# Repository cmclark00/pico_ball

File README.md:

# pico_ball — carry your Pokémon out of a real cartridge

Turn a [`weimanc/game-boy-zero-link-board`](https://github.com/weimanc/game-boy-zero-link-board)
(an RP2040‑Zero USB↔Game Boy Link‑Cable adapter) into a tool that talks to your
**physical Pokémon Blue** cartridge over the link port and **copies a Pokémon off
it into a file you can carry around** — without losing it from the cartridge.

> **Status:** Path A (PC‑tethered extract + inject) is **working on real
> hardware** — both directions, non‑destructive. Path B (fully standalone, no‑PC
> pocket vault) is **built and compiling** (`firmware/prebuilt/pico_ball_vault.uf2`);
> its on‑device trade FSM awaits a hardware bring‑up pass — see
> [firmware/path-b-standalone/README.md](firmware/path-b-standalone/README.md).

## The one important mental‑model correction

Your board is **not** where the Pokémon "lives." It is a *bridge*: it speaks the
Game Boy link‑cable serial protocol on one side and USB on the other. The board
pretends to be a second Game Boy so your cartridge will trade with it. Where the
Pokémon actually gets **stored** is a software choice:

- **Path A — tethered:** the storage is a file on your laptop (`vault/`). You carry
  the laptop/phone. Proven, low‑risk, working today.
- **Path B — standalone:** the storage is the RP2040's own on‑board flash. Press a
  button, it does the trade by itself, the Pokémon lives on the board. You carry
  the board. This is the real dream — and it has been proven possible on similar
  hardware (the Flipper Zero Pokémon‑trading app does exactly this).

## How a Game Boy trade actually works (the part that makes this possible)

- Pokémon Blue is a Game Boy (Gen 1) game. A **GBA plays it in GB‑compatibility
  mode** and the link port behaves as the classic GB serial link, so your board's
  GBC/GBA edge connector works for it.
- A trade is a well‑documented **state machine** (Adan Scotney's spec): handshake →
  random‑seed exchange → two patch lists → a 415‑byte "trade block" containing your
  whole party → pick a Pokémon (`0x60 + index`) → swap.
- **Key trick for *copying without losing*:** the cartridge sends its *entire party*
  (the trade block) *before* either side confirms the swap. We read that block,
  save every Pokémon in it, and then **cancel** the trade. The cartridge keeps
  everything; we keep a copy. Non‑destructive.

## Quick start (Path A)

```bash
# 1. One-time setup: Python deps + the proven trade engine we build on
./scripts/setup.sh

# 2. Flash the board (see firmware/README.md) — stacksmashing gb-link-firmware

# 3. Plug board -> laptop (USB) and board -> GBA link port. Boot Pokémon Blue,
#    go to a Pokémon Center -> Cable Club -> Trade Center, sit at the table.

# 4. Copy your party into the vault (non-destructive). The ./pb launcher runs
#    the host tools in the project venv, so there's nothing to activate:
./pb extract              # saves vault/*.pk1 + vault/*.json, then cancels
./pb extract --gen 2      #   ...or Gold/Silver/Crystal (Gen 2 -> *.pk2)

# Gen 3 (Ruby/Sapphire/Emerald/FireRed/LeafGreen): flash the reconfigurable
# firmware (third_party/gen3/gbusb_reconfigurable.uf2), then multiboot the
# GBA-side trade program and capture:
./pb gen3-boot            # upload Gen3-to-GenX into the GBA's RAM
./pb extract --gen 3      # saves vault/*.pk3 (PKHeX party format)

# 5. See what you've captured (no device needed):
./pb list                 # decoded table: gen, species, level, OT, nickname

# 6. (Optional) Trade a vaulted Pokémon back INTO a cartridge:
./pb inject               # pick from a decoded list; the cart's given-up mon is
                          # auto-saved to the vault, so nothing is lost

# 7. (Optional) Export your captures as a .sav (opens in PKHeX/emulators):
./pb export-sav           # Gen 1 -> vault/pico_ball.sav  (--gen 2 for G/S/C)
```

> Prefer the raw scripts? Every `./pb <cmd>` maps to `python host/<cmd>.py`
> after `source host/.venv/bin/activate` — the launcher just saves the typing.

See **[docs/PLAN.md](docs/PLAN.md)** for the full phased plan, and
**[docs/research.md](docs/research.md)** for everything the design is based on
(with sources).

## Gen 1/2 → Gen 3 "transfer" (Pal-Park-style recreation)

The Game Boy and GBA games have **no native link** — Nintendo's first official
forward-migration was Gen 3 → Gen 4 (Pal Park). So a literal transfer is
impossible, but we can *recreate* a captured Gen 1/2 Pokémon as a legal Gen 3
`.pk3`, exactly like **[Poké Transporter GB](https://github.com/GearsProgress/Poke_Transporter_GB)**
does, using its **[Pokémon Community Conversion Standard](https://github.com/GearsProgress/Pokemon-Community-Conversion-Standard)**
(PCCS, MIT). Species, level, moves, nickname, and OT are kept; PID / IVs / nature
/ ability are generated to match.

There are two ways to do it:

**A. Onto a real Gen 3 cartridge — no flashcart, no PC** (standalone board). The
board **multiboots Poke Transporter GB** into a GBA over the link cable, then
offers a stored Gen 1/2 mon to it; PTGB converts it and writes it to the Gen 3
cartridge's save. You only need the board, a GBA, a Gen 3 cart, and the cable —
hand someone a flashed board and they're set. See
[firmware/path-b-standalone/README.md](firmware/path-b-standalone/README.md)
("Transfer Gen 1/2 → Gen 3"). From the cartridge, the mon rides the official Pal
Park → … → HOME chain on real hardware. **This path is not working yet:** the
board can multiboot PTGB, but PTGB expects to talk to a real Game Boy game (it
clocks the link itself and reads the game's PC boxes through its own protocol),
not to a trade partner — see the status note in that README. What the board can
do instead is convert a stored Gen 1/2 Pokémon itself (it runs PCCS) and trade it
into the Gen 3 cartridge through Gen3-to-GenX; that is built and host-tested but
not yet tried on hardware ("Send a Gen 1/2 Pokémon to a Gen 3 cartridge" in that
README).

**B. As a file, for PKHeX/emulators.** `scripts/setup.sh` also builds a host
converter (PCCS), so pulling captures off the board auto-writes a Gen 3 box `.pk3`
for each Gen 1/2 mon:

```bash
./pb import                         # vault/dex/*.pk1 + vault/dex/gen3/*.pk3
```

The `.pk3` files are 80-byte box records — drag them straight into **PKHeX** (or a
Gen 3 save). Run `python tools/test_pccs.py` to self-check the conversion.

Both use the same engine (PCCS), so they produce the same conversion. The endgame
is **Pokémon HOME**: a Gen 1/2 mon → Gen 3 → (Pal Park) Gen 4 → 5 → 6/7 → Bank →
HOME, legal at each hop. The board does the one step with no official path (Gen
1/2 → Gen 3); the rest is the standard forward-migration chain.

## View Pokémon straight from the device (WebUI)

With the standalone (Path B) firmware flashed, you don't need to copy anything to
disk to look at your captures:

```bash
./pb webui                # serves webui/ — open http://localhost:8000 in Chrome/Edge
```

Click **Connect device**, pick **"pico_ball vault"** from the WebUSB chooser, and
the page reads the stored records over **WebUSB** and decodes the Pokémon **in the
browser** — sprite, level, HP, moves, OT. Works on desktop and Android Chrome. See
[webui/README.md](webui/README.md).

## Optional 3.2-inch touch front panel

The Hosyond `E32R32P` ESP32-32E display (ST7789P3 + XPT2046) can act as a
standalone front panel. It lists the Pico's vault over a three-wire UART link and
lets you tap a Gen 3 Pokémon, multiboot the GBA trade program, and inject that
exact vault slot without a PC. See
[firmware/display-esp32/README.md](firmware/display-esp32/README.md) for the exact
board identity, wiring, builds, flashing, and first-hardware acceptance test.

## Repository layout

```
docs/                      Plan, research, protocol, hardware + flashing guide
firmware/                  Which firmware to flash (Path A) + Path B design
  display-esp32/           Hosyond E32R32P touchscreen vault picker
host/                      Path A: the PC-side extractor (Python)
  picovault/               Our code: local no-server connection, save logic
  extract.py               Main entrypoint: copy party -> vault -> cancel
scripts/setup.sh           Clones the pinned trade engine + sets up a venv
vault/                     Where copied Pokémon land (.pk1 raw + .json decoded)
third_party/               (created by setup.sh) the MIT trade engine we reuse
```

## Credits / things we build on

- [`weimanc/game-boy-zero-link-board`](https://github.com/weimanc/game-boy-zero-link-board) — the hardware (MIT).
- [`stacksmashing/gb-link-firmware`](https://github.com/stacksmashing/gb-link-firmware) — RP2040 link‑cable firmware (MIT).
- [`Lorenzooone/PokemonGB_Online_Trades`](https://github.com/Lorenzooone/PokemonGB_Online_Trades) — the proven, sanity‑checked Gen 1/2/3 trade engine we reuse for Path A (MIT).
- [`GearsProgress/Poke_Transporter_GB`](https://github.com/GearsProgress/Poke_Transporter_GB) + [`Pokemon-Community-Conversion-Standard`](https://github.com/GearsProgress/Pokemon-Community-Conversion-Standard) — the Gen 1/2 → Gen 3 conversion we vendor + build for the "transfer" feature (MIT).
- [`kbembedded/Flipper-Zero-Game-Boy-Pokemon-Trading`](https://github.com/kbembedded/Flipper-Zero-Game-Boy-Pokemon-Trading) — proof + reference that the standalone Path B is feasible (MIT).

## License

[MIT](LICENSE) for this project's own code. Vendored third‑party files (the Pico
SDK PIO helpers under `firmware/path-b-standalone/`) retain their own BSD‑3‑Clause
headers; the reused trade engine and bridge firmware are MIT and fetched/built at
setup time rather than redistributed here. See [LICENSE](LICENSE) for details.

## Continuous integration

`.github/workflows/firmware.yml` builds the standalone firmware on every change to
`firmware/path-b-standalone/` (Pico SDK pinned to a fixed version) and uploads the
`pico_ball_vault.uf2` as a workflow artifact. Trigger it manually from the Actions
tab via *Run workflow*.

## Legal / ethics

This copies *your own* Pokémon from *your own* cartridge to *your own* storage for
personal backup and portability. It does not modify or distribute Nintendo's game
code. Don't use it to clone Pokémon into trades with other people without telling
them.

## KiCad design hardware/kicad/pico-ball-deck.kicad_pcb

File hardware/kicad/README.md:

# pico-ball deck — KiCad files

`pico-ball-deck.kicad_pcb` is the **fully routed rev-A board**:
**0 DRC violations, 0 unconnected items** (KiCad 8 `kicad-cli pcb drc`).
GND pours on both layers with stitching vias. Open it in KiCad 8+
(`pcbnew pico-ball-deck.kicad_pcb`).

## Routing pipeline (reproducible, Docker only — no local KiCad/Java)

```bash
./route.sh
```

runs: `generate_board.py` (placement + netlist) → `add_preroutes.py`
(hand-routed hard nets + GND stitch vias, see below) → DSN export →
**Freerouting 1.9** (Java 21 container) → SES import + zone fill
(`import_ses.py`) → DRC. ~4 minutes end to end.

Requires `../reference/game-boy-zero-link-board/` — clone of
https://github.com/weimanc/game-boy-zero-link-board, MIT — for the J1 link
connector, BOB-12009 and Pico module footprints.

**Why pre-routes:** the autorouter reliably fails 10 specific connections on
this board (bottom-row→header climbers boxed in by its own power buses, the
0.71 mm U2/pin-20 pinch, the long PSC/PSI/PSO link bus). `add_preroutes.py`
places those by hand on the fresh board — every path hand-verified at
≥ 0.25 mm copper / ≥ 0.3 mm edge clearance — and Freerouting routes the
remaining ~20 easy nets around them.

## What's verified

- Outline/holes/header from the official Pi Zero mechanical drawing
  (65×30 mm, r3 corners, M2.5 drilled 2.75 mm at 58×23 grid, header pin 1 at
  (8.37, 4.77), even pins on the edge row).
- PiSugar pogo pads cloned from the official **Zero 2 W test-pad drawing**
  (both 5V pads + both adjacent GND pads, 2.2 mm bottom copper) — whichever
  pads the PiSugar's pins actually touch, they hit the right net. I2C pogo
  pins contact the underside of header pins 3/5 (through-hole pads).
- J1 link tab machine-diffed against the proven weimanc board's J1
  (`gb-link-socket`, the small GBC-plug tab): congruent in every dimension —
  6.5 mm wide tab, 6.5 mm protrusion, pad centers 3.5 mm from the body edge
  / 3.0 mm from the tip, 1×5 mm pads at 2 mm pitch, 3 contacts per face,
  same pad→net map (1=GBVCC 2=SO 3=SI 4=SD 5=SC 6=GND). A no-pour rule area
  keeps the GND zones off the tab (matching the reference; the plug slides
  over it). Note the weimanc board also carries a second, larger
  `dmg-link-socket` tab (2×8 mm pads at 2.5/2.6 mm pitch) for the original
  DMG plug — this board only has the small-plug tab.
- Link stays on GP0/1/2(/3) through the BOB-12009 — matches
  `firmware/path-b-standalone/gb_link.c` unchanged.
- Pad positions machine-audited (all inside outline, USB end at right edge,
  no single-pad nets).

## Known rev-A tradeoffs

- **3-point mounting:** the Pico 2 W module covers the bottom-right M2.5 hole
  (a 21 mm module can't fit between the corner keepouts). That hole is
  **omitted** — DRC showed its drill would cut through the module's pads
  38–40. PiSugar + HAT mount on the other three standoffs, which is
  mechanically fine for these masses.
- No onboard buttons/LED: the LCD HAT's joystick + 3 keys are the UI; reset =
  power-cycle; BOOTSEL via `picotool reboot -u` or pop the HAT off. A
  side-actuated reset switch + WS2812 are rev-B candidates (GP15/GP26 kept
  free for them).
- D1/C1/JP1 sit on the bottom side (clear of the pogo zone); JP1 bridges
  VBUS→5V rail only for HAT-without-PiSugar use.
- **USB recessed 1.0 mm:** the Pico's castellation pads extend 2.65 mm past
  each pin row, which pins the module between the header pad row and the r3
  board corner. It sits 1.0 mm in from the right edge; the micro-USB shell
  protrudes ~1.3 mm past the module edge, so cables still seat.
- **U1 pins 34/36/37 have no through-holes** (top SMD pads only): the
  PiSugar's GND pogo pins land exactly on the back of that stretch of pin
  row, and plated holes there would short 3V3/3V3_EN to GND. The module
  solders by castellation, so nothing is lost.
- **U1 SWD pads (41–43) are plain through-holes** (castellation extensions
  removed — they crowded U2). Debug wires can still be soldered through.

## Remaining work before fab

1. ~~Route it~~ ✅ routed, DRC clean (see pipeline above).
2. ~~Sanity-check the tab~~ ✅ machine-diffed against the weimanc board's
   small-plug tab — congruent (see above). Still worth one physical dry fit.
3. Optional: draw the schematic to match (the netlist source of truth is
   `generate_board.py`).
4. ~~Generate gerbers~~ ✅ `pico-ball-deck-rev-a-gerbers.zip` (9 layers +
   Excellon drill + map, Protel extensions — upload straight to JLCPCB).
   Regenerate with `kicad-cli pcb export gerbers/drill` in the same Docker
   image; `add_tab_keepout.py` documents the tab rule area (now also baked
   into `import_ses.py`).

Note: the copper-to-edge DRC rule is 0.25 mm (JLC's minimum for routed
edges is 0.2 mm); net clearance is 0.25 mm everywhere, power nets 0.5 mm
track / GND-VSYS-VBUS-3V3-5V-GBVCC in the Power class.

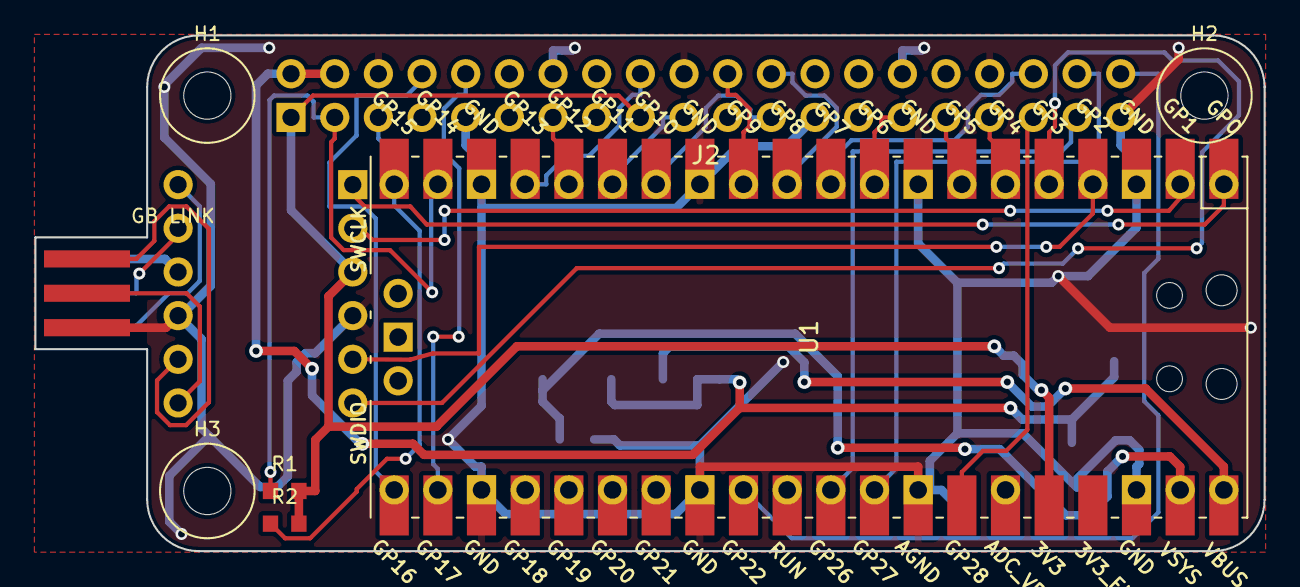
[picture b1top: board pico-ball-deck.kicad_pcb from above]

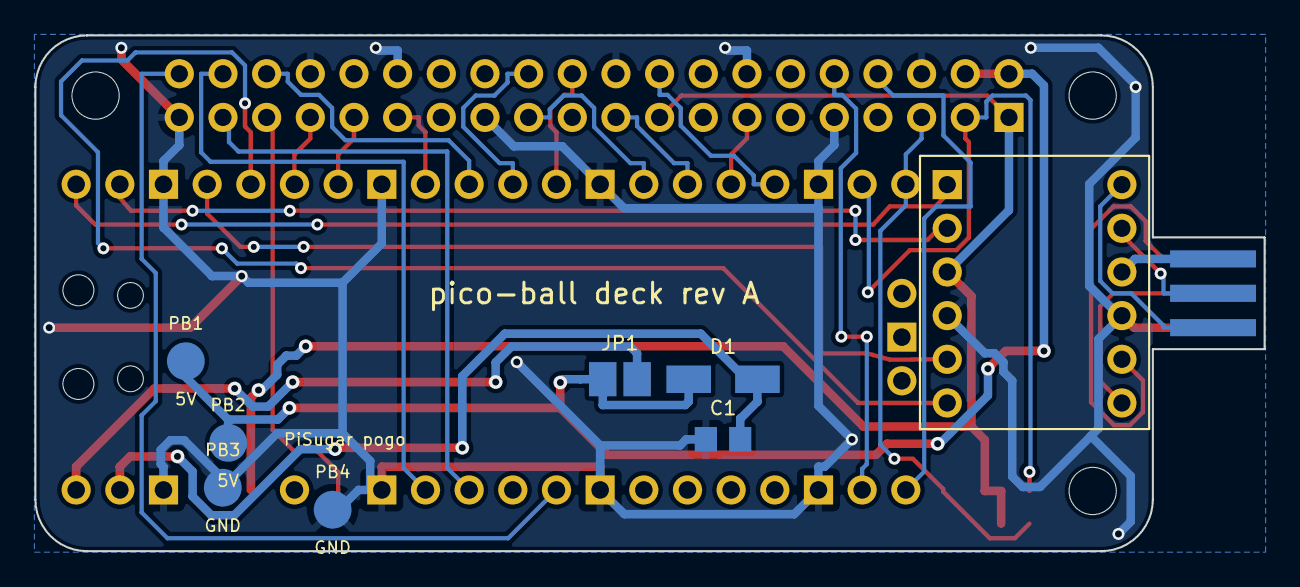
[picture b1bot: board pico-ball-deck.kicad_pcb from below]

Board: 2 copper layers, 71.5 x 30.0 mm, 16 parts (8 on the bottom side), 32 nets.

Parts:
C1: 10uF; C_0805
D1: SS34; D_SMA
H1, H2, H3: M2.5; MountingHole_2.75mm_M2.5
J1: GBA_Link; gb-link-socket
J2: Pi HAT header; PinHeader_2x20_P2.54mm_PiZero
JP1: VBUS->5V; SolderJumper
PB1, PB2: 5V; PiSugar_PogoPad_D2.2mm
PB3, PB4: GND; PiSugar_PogoPad_D2.2mm
R1, R2: 4k7; R_0603
U1: RPi_Pico_SMD_TH_1; RPi_Pico2W_SMD_TH
U2: BOB-12009

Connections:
+3V3: J2.1, J2.17, R1.2, R2.2, U1.36, U2.3 (LV)
+5V_SUGAR: D1.2, J2.2, J2.4, JP1.2, PB1.1, PB2.1
GBVCC: J1.1, U2.9 (HV)
GND: C1.2, J1.6, J2.6, J2.9, J2.14, J2.20, J2.25, J2.30, J2.34, J2.39, PB3.1, PB4.1, U1.3, U1.8, U1.13, U1.18, U1.23, U1.28, U1.33, U1.38, U2.4 (GND_1), U2.10 (GND_2)
I2C_SCL: J2.5, R2.1, U1.20
I2C_SDA: J2.3, R1.1, U1.19
JOY_DOWN: J2.35, U1.34
JOY_LEFT: J2.29, U1.9
JOY_PRESS: J2.33, U1.6
JOY_RIGHT: J2.37, U1.31
JOY_UP: J2.31, U1.7
KEY1: J2.40, U1.29
KEY2: J2.38, U1.32
KEY3: J2.36, U1.10
LCD_BL: J2.18, U1.17
LCD_CS: J2.24, U1.11
LCD_DC: J2.22, U1.12
LCD_MOSI: J2.19, U1.15
LCD_RST: J2.13, U1.16
LCD_SCK: J2.23, U1.14
PSC: U1.1, U2.1 (LV1)
PSD: U1.5, U2.6 (LV4)
PSI: U1.2, U2.2 (LV2)
PSO: U1.4, U2.5 (LV3)
SC: J1.5, U2.7 (HV1)
SD: J1.4, U2.12 (EL)
SI: J1.3, U2.8 (HV2)
SO: J1.2, U2.11 (HV3)
UART_RX: J2.10, U1.22
UART_TX: J2.8, U1.21
VBUS: JP1.1, U1.40
VSYS: C1.1, D1.1, U1.39

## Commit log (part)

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2026-06-16 rking on
2026-06-16 Fix mobile Chrome Web Serial support and CI build for multiboot source
2026-06-16 Fix mobile Chrome device discovery by passing explicit USB filters to requestPort
2026-06-16 Update requestPort filter to use standard Raspberry Pi Pico VID (0x2E8A)
2026-06-16 Remove vendor filter from requestPort to allow any CDC device
